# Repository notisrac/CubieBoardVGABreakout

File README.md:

# VGA breakout board for Cubieboard

PCB for the vga output of the cubieboard: [https://github.com/cubieplayer/Cubian/wiki/VGA-output](https://github.com/cubieplayer/Cubian/wiki/VGA-output)

## BOM
* 1x VGA connector
* 2x BAT54s Shottky diodes (note: you need the "s" version)
* 3x 75ohm resistor
* 1x 74ACT08D (note: you need the ACT version for its speed)
* 1x 100nF capacitor
* Pin headers

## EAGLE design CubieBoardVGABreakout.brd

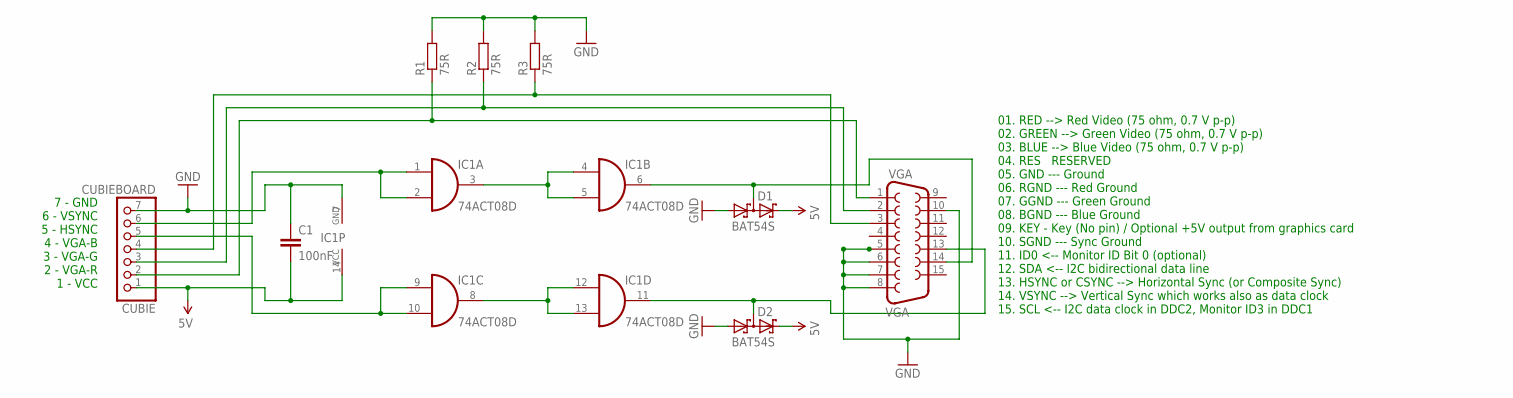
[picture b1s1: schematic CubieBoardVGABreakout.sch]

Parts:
C1: 100nF; 0805
CUBIE: CUBIEBOARD; 1X07
D1, D2: BAT54S; SOT23
IC1: 74ACT08D; SO14
R1, R2, R3: 75R; 0204V
VGA: VGA; HDF15H

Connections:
5V: C1.2, CUBIE.1, D1.2 (C2), D2.2 (C2), IC1.14 (VCC)
GND: C1.1, CUBIE.7, D1.1 (A1), D2.1 (A1), IC1.7 (GND), R1.2, R2.2, R3.2, VGA.5, VGA.6, VGA.7, VGA.8, VGA.10
unnamed: CUBIE.6, IC1.1 (I0), IC1.2 (I1)
unnamed: CUBIE.5, IC1.9 (I0), IC1.10 (I1)
unnamed: IC1.3 (O), IC1.4 (I0), IC1.5 (I1)
unnamed: IC1.8 (O), IC1.12 (I0), IC1.13 (I1)
unnamed: D2.3 (C1A2), IC1.11 (O), VGA.13
unnamed: D1.3 (C1A2), IC1.6 (O), VGA.14
VGA-B: CUBIE.4, R3.1, VGA.3
VGA-G: CUBIE.3, R2.1, VGA.2
VGA-R: CUBIE.2, R1.1, VGA.1

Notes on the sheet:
7 - GND 6 - VSYNC 5 - HSYNC 4 - VGA-B 3 - VGA-G 2 - VGA-R 1 - VCC
01. RED --> Red Video (75 ohm, 0.7 V p-p) 02. GREEN --> Green Video (75 ohm, 0.7 V p-p) 03. BLUE --> Blue Video (75 ohm, 0.7 V p-p) 04. RES RESERVED 05. GND --- Ground 06. RGND --- Red Ground 07. GGND --- Green Ground 08. BGND --- Blue Ground 09. KEY - Key (No pin) / Optional +5V output from graphi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

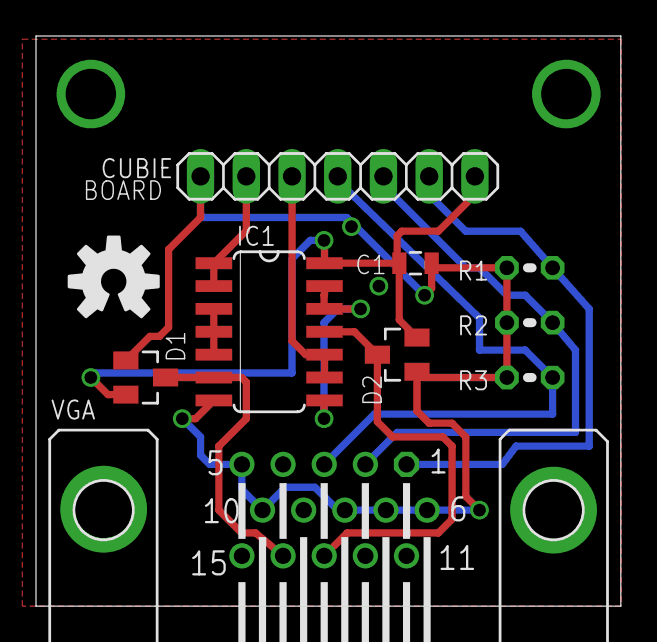
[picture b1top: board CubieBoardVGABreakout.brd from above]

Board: 2 copper layers, 32.5 x 31.7 mm, 10 parts (0 on the bottom side), 11 nets.

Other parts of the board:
U$1: OSHW-LOGO-M

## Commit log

2016-02-07 - Fixed: forgot to place a file into the Manufacture dir
2018-07-27 Fixed README issues
2018-07-28 Added GA beacon to the README
2018-07-29 Removed epf file

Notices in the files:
parts and their libraries:
SparkFun-Passives: Licensing: Creative Commons ShareAlike 4.0 International - https://creativecommons.org/licenses/by-sa/4.0
